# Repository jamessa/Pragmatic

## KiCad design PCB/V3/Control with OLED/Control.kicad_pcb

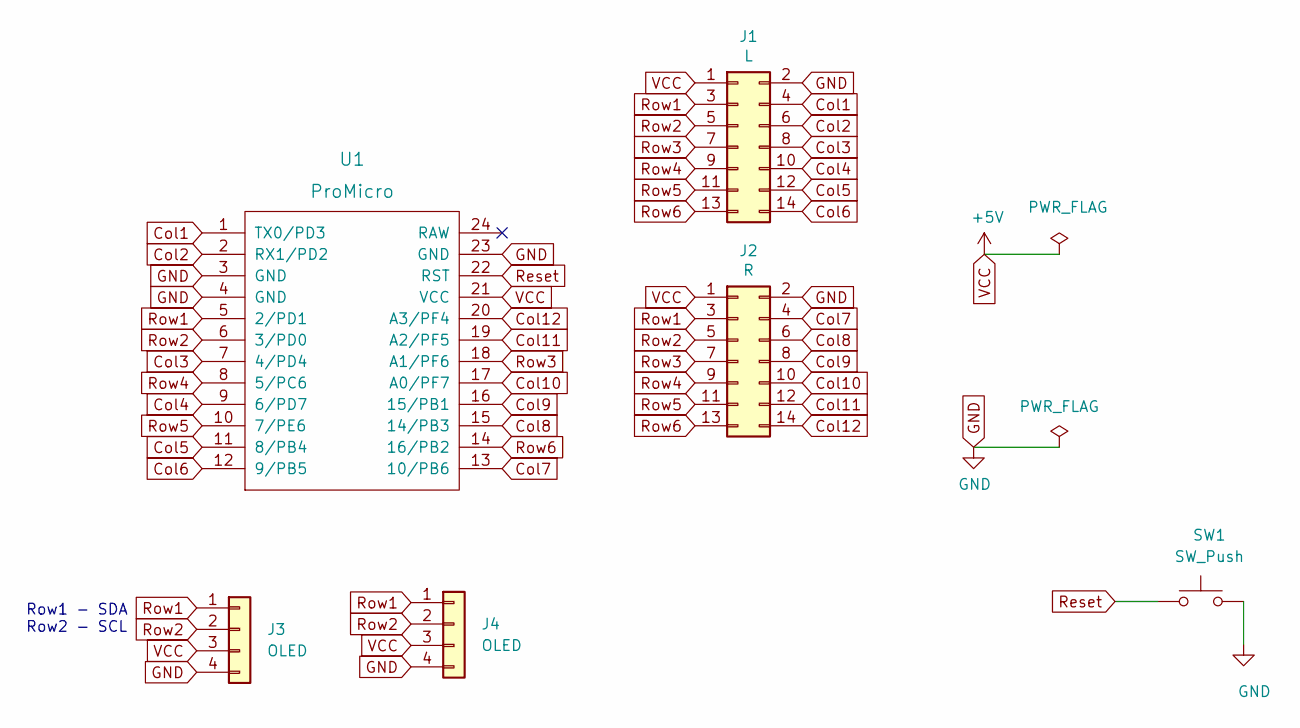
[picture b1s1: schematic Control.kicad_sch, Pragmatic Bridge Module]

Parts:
J1: L; IDC-Header_2x07_P2.54mm_Vertical; LCSC C3406
J2: R; IDC-Header_2x07_P2.54mm_Vertical; LCSC C3406
J3, J4: OLED; SSD1306_OLED-0.91-128x32
SW1: SW_Push; SW_PUSH_6mm; LCSC C620316
U1: ProMicro; ProMicro Type C Reversed

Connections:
Col1: J1.4, U1.1 (TX0/PD3)
Col2: J1.6, U1.2 (RX1/PD2)
Col3: J1.8, U1.7 (4/PD4)
Col4: J1.10, U1.9 (6/PD7)
Col5: J1.12, U1.11 (8/PB4)
Col6: J1.14, U1.12 (9/PB5)
Col7: J2.4, U1.13 (10/PB6)
Col8: J2.6, U1.15 (14/PB3)
Col9: J2.8, U1.16 (15/PB1)
Col10: J2.10, U1.17 (A0/PF7)
Col11: J2.12, U1.19 (A2/PF5)
Col12: J2.14, U1.20 (A3/PF4)
GND: J1.2, J2.2, J3.4, J4.4, SW1.2, U1.3 (GND), U1.4 (GND), U1.23 (GND)
Reset: SW1.1, U1.22 (RST)
Row1: J1.3, J2.3, J3.1, J4.1, U1.5 (2/PD1)
Row2: J1.5, J2.5, J3.2, J4.2, U1.6 (3/PD0)
Row3: J1.7, J2.7, U1.18 (A1/PF6)
Row4: J1.9, J2.9, U1.8 (5/PC6)
Row5: J1.11, J2.11, U1.10 (7/PE6)
Row6: J1.13, J2.13, U1.14 (16/PB2)
VCC: J1.1, J2.1, J3.3, J4.3, U1.21 (VCC)

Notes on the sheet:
Row1 - SDA Row2 - SCL

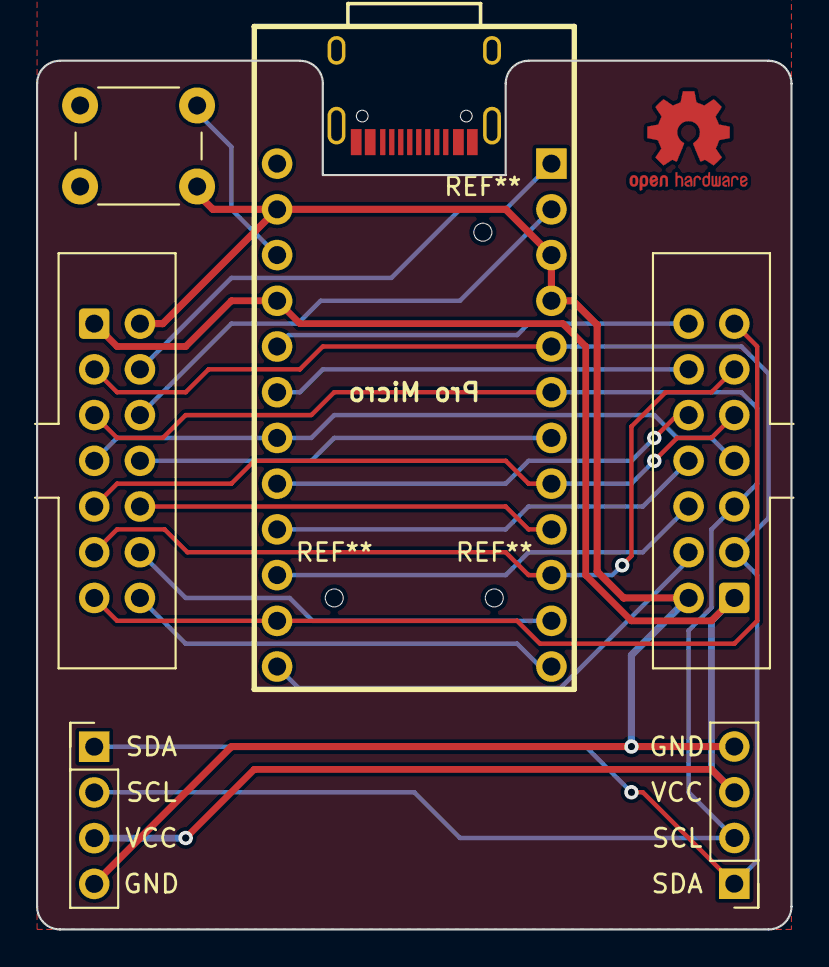
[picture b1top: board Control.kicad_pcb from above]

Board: 2 copper layers, 41.9 x 48.3 mm, 8 parts (1 on the bottom side), 21 nets.

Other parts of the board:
L1: JLC Legend
Logo1: OSHW-Logo2_7.3x6mm_Copper

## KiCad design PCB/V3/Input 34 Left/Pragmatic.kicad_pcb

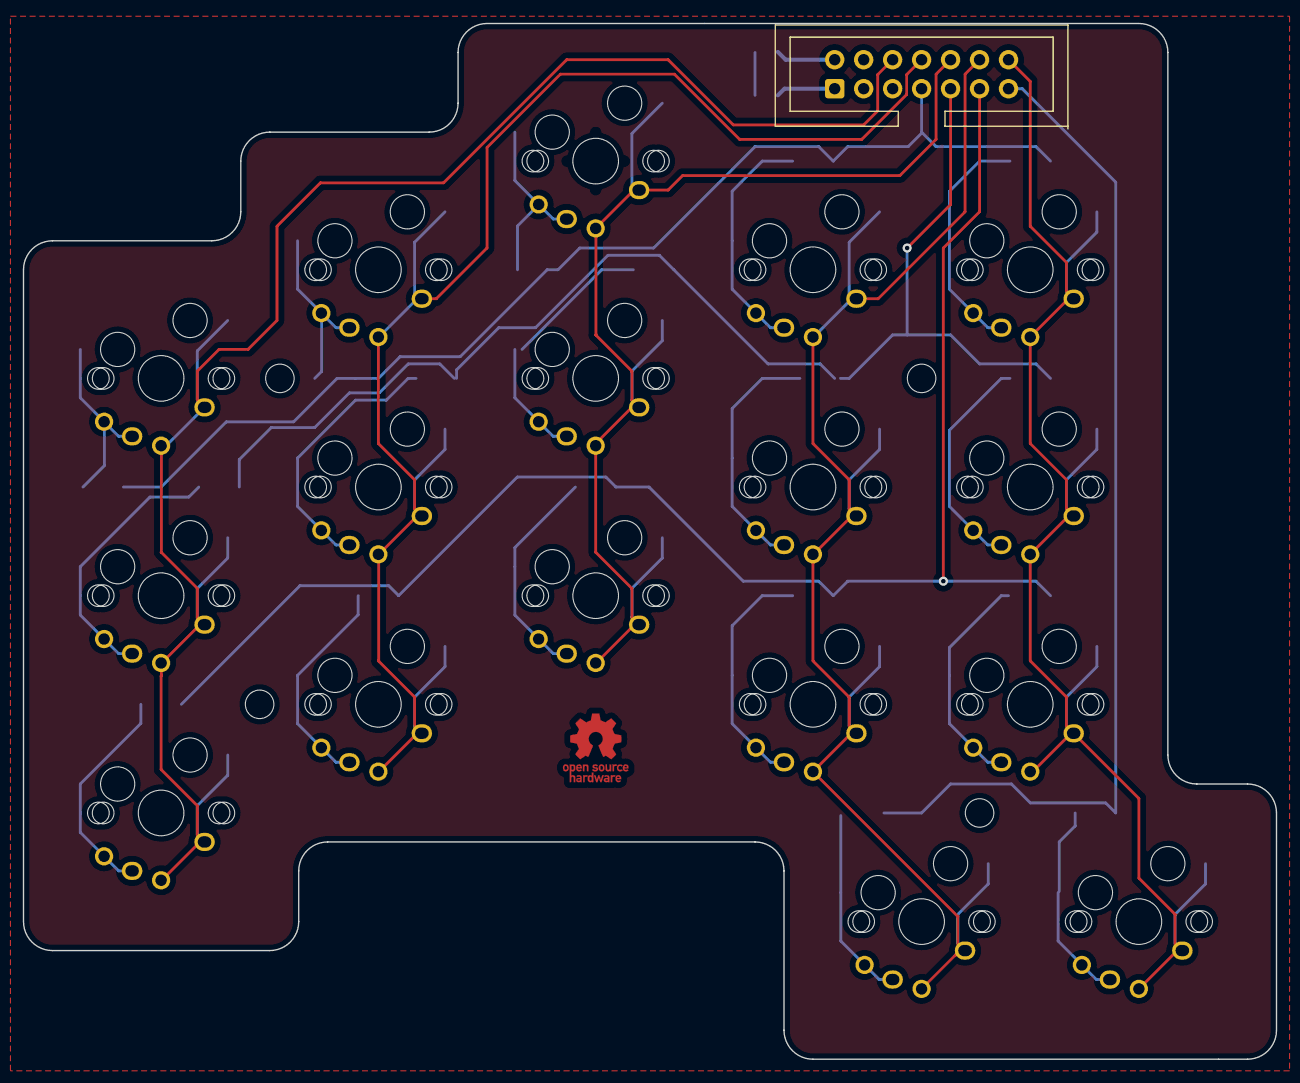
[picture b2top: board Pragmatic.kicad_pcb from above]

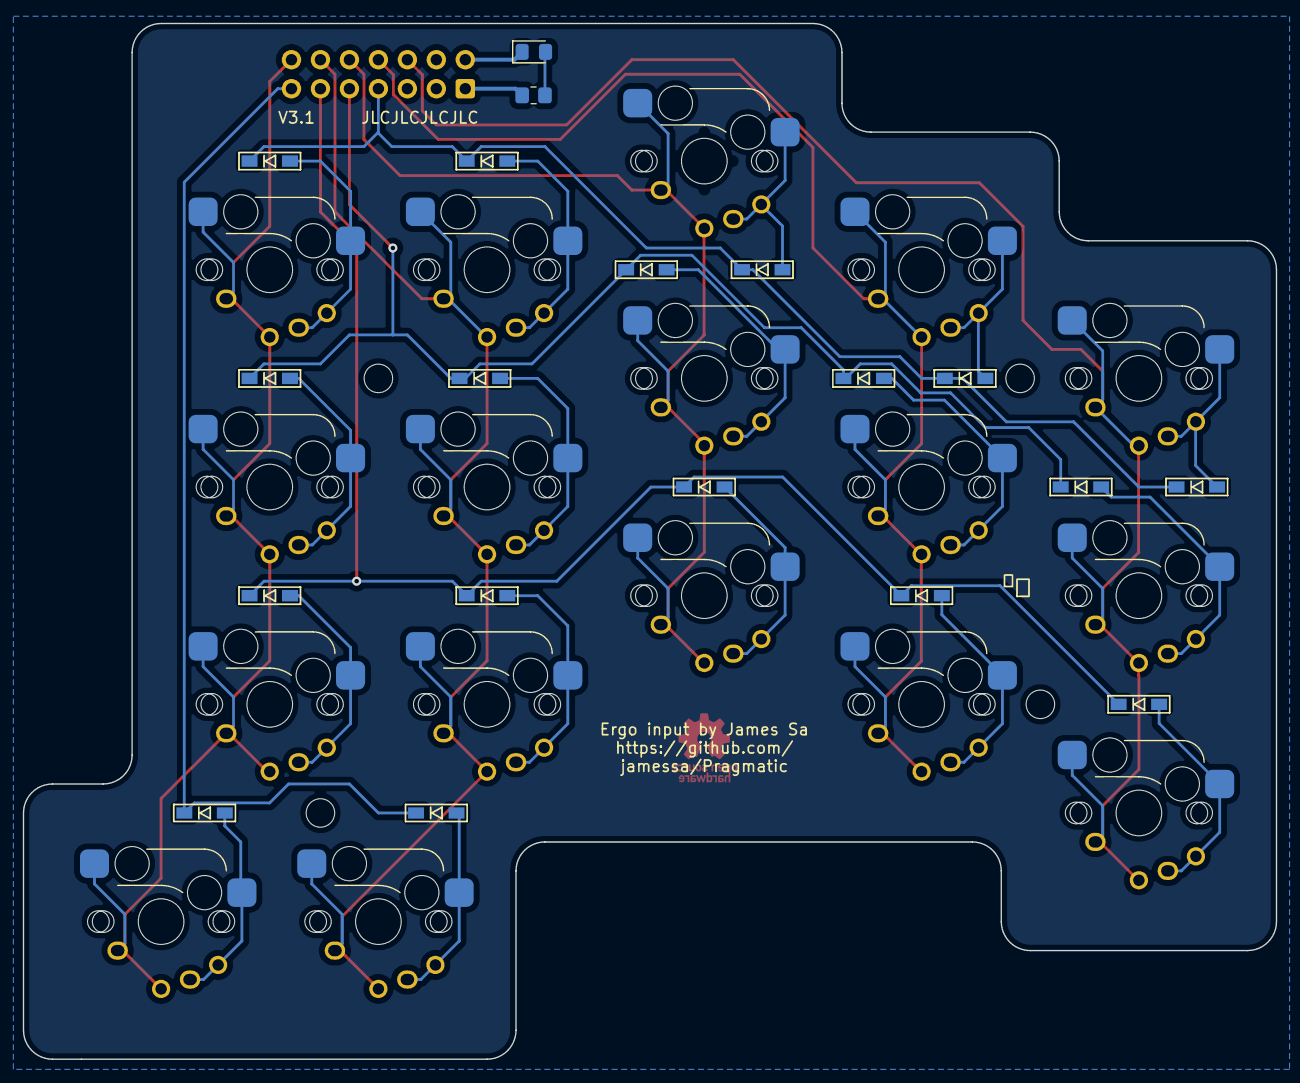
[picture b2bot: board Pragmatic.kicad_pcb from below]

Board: 2 copper layers, 109.9 x 90.8 mm, 42 parts (36 on the bottom side), 29 nets.

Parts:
D1, D2, D3, D4, D5, D7, D8, D9, D10, D11, D13, D14, D15, D16, D17, D22, D23: 1N4148; D3_SMD_v2
D37: White LED; LED_0805_2012Metric_Pad1.15x1.40mm_HandSolder
H1, H2, H3, H4: MountingHole; MountingHole_2.5mm
J1: Hand-Soldering; IDC-Header_2x07_P2.54mm_Vertical
LOGO1: Logo_Open_Hardware_Small; OSHW-Logo_5.7x6mm_Copper
R1: 1.5K 1/8W; R_0805_2012Metric_Pad1.20x1.40mm_HandSolder
SW1, SW2, SW3, SW4, SW5, SW7, SW8, SW9, SW10, SW11, SW13, SW14, SW15, SW16, SW17, SW22, SW23: SW_Push; MX_Hotswap_MX_Choc_Solder

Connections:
Col2: J1.6, SW1.2, SW7.2, SW13.2
Col3: J1.8, SW2.2, SW8.2, SW14.2
Col4: J1.10, SW3.2, SW9.2, SW15.2
Col5: J1.12, SW4.2, SW10.2, SW16.2, SW22.2
Col6: J1.14, SW5.2, SW11.2, SW17.2, SW23.2
GND: D37.1 (K), J1.2
unnamed: D1.2 (A), SW1.1
unnamed: D2.2 (A), SW2.1
unnamed: D3.2 (A), SW3.1
unnamed: D4.2 (A), SW4.1
unnamed: D5.2 (A), SW5.1
unnamed: D7.2 (A), SW7.1
unnamed: D8.2 (A), SW8.1
unnamed: D9.2 (A), SW9.1
unnamed: D10.2 (A), SW10.1
unnamed: D11.2 (A), SW11.1
unnamed: D13.2 (A), SW13.1
unnamed: D14.2 (A), SW14.1
unnamed: D15.2 (A), SW15.1
unnamed: D16.2 (A), SW16.1
unnamed: D17.2 (A), SW17.1
unnamed: D22.2 (A), SW22.1
unnamed: D23.2 (A), SW23.1
unnamed: D37.2 (A), R1.2
Row3: D1.1 (K), D2.1 (K), D3.1 (K), D4.1 (K), D5.1 (K), J1.7
Row4: D7.1 (K), D8.1 (K), D9.1 (K), D10.1 (K), D11.1 (K), J1.9
Row5: D13.1 (K), D14.1 (K), D15.1 (K), D16.1 (K), D17.1 (K), J1.11
Row6: D22.1 (K), D23.1 (K), J1.13
VCC: J1.1, R1.1
